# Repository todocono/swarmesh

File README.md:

# Swarm Mesh Research Team

To read the latest research published by the team, access: 
https://github.com/todocono/swarmesh/blob/master/DOC/Paper/SWARM_2019_paper.pdf

To work with the PCB, you will need the latest version of Eagle: https://www.autodesk.com/products/eagle/overview 

To work with the 3D models, you will need Fusion 360 and access the following files:
https://a360.co/2WSIKhr
https://a360.co/2x0crTh

To work with the IDE and latest version, you need:

- Arduino IDE 1.8.9
- CP2102 driver (https://www.silabs.com/products/development-tools/software/usb-to-uart-bridge-vcp-drivers)
- ESP32 Arduino installed 1.0.2 (add https://raw.githubusercontent.com/espressif/arduino-esp32/gh-pages/package_esp32_index.json)
- FastLED library 3.3.2 (from Boards Manager)
- PainlessMesh 1.4.2 (from Boards Manager)
- ArduinoJson 6.12.0 (from Boards Manager)
- TaskScheduler 3.0.2 (from Boards Manager, not really used)
- AsyncTCP (manual install https://github.com/me-no-dev/AsyncTCP)
- AsyncUDP (available in ESP32's arduino library)

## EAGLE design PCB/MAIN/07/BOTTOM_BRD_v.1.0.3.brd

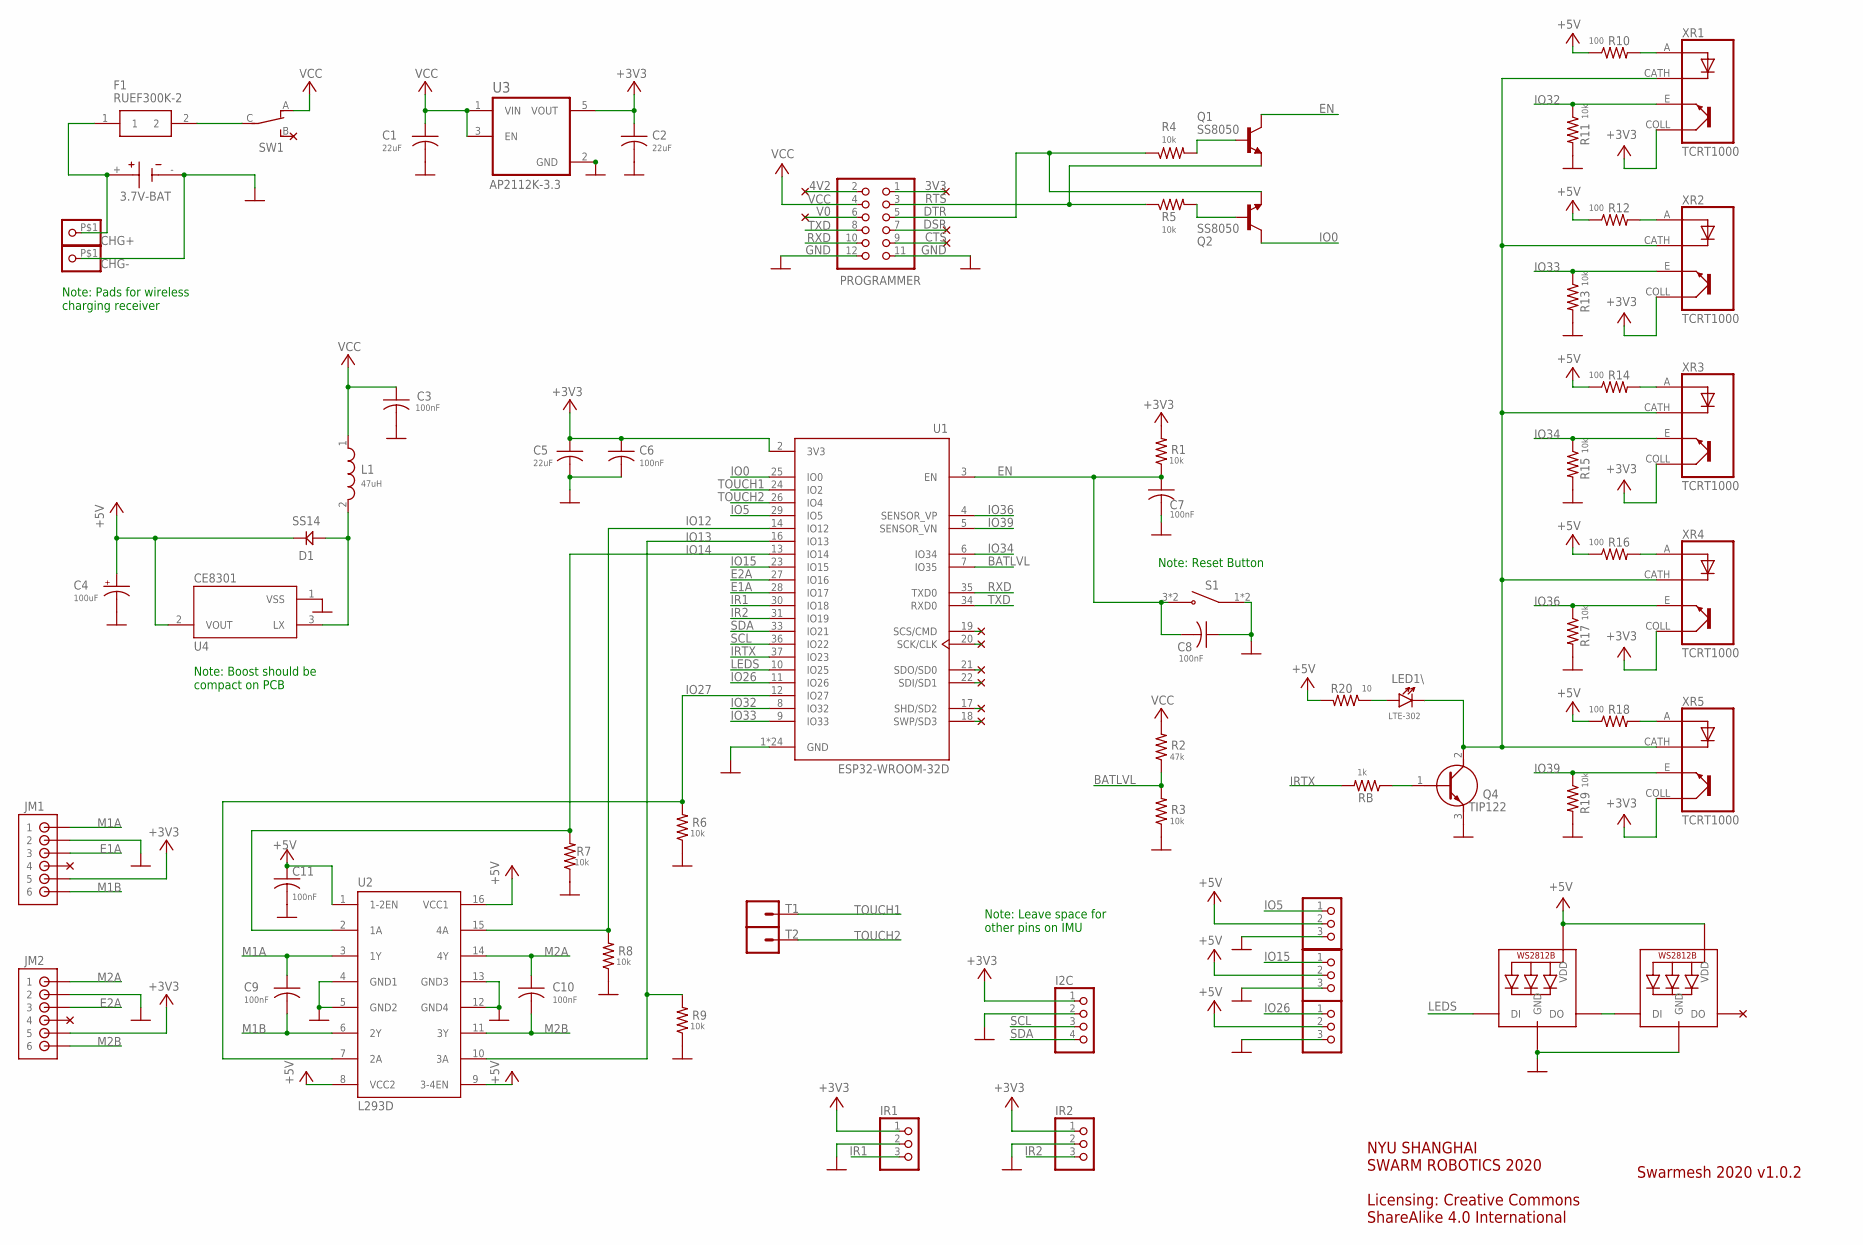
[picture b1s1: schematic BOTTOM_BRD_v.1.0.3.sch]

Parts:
BT: 3.7V-BAT; BAT_6S-AA
C1, C2, C5: 22uF; C0805
C3, C6, C7, C8, C9, C10, C11: 100nF; C0805
C4: 100uF; 153CLV-0605
CHARGING: WS2812B5050; WS2812B
CHG+: PINHD-1X1-BIGPOGO; 1X1-BIGPOGO
CHG-: PINHD-1X1-BIGPOGO; 1X1-BIGPOGO
D1: SS14; DO214
F1: RUEF300K-2; RUEF300K2
GPIO5, GPIO15, GPIO26: PINHD-1X3; 1X03
I2C: PINHD-1X4; 1X04
IR1, IR2: PINHD-1X3; 1X03
JM1, JM2: B6B-ZR
L1: 47uH; INDP5858X480N
LED1\: LTE-302
PROGRAMMER: PINHD-2X6; 2X06
Q1, Q2: SS8050; SOT23
Q4: TIP122; TO270P460X1020X2008-3P
R1, R3, R4, R5, R6, R7, R8, R9, R11, R13, R15, R17, R19: 10k; M0805
R2: 47k; M0805
R10, R12, R14, R16, R18: 100; M0805
R20: 10; M0805
RB: 1k; M0805
S1: 2-1437565-9; SW_2-1437565-9
STATE: WS2812B5050; WS2812B
SW1: CS12ANW03
T1, T2: CONN_01SPRING-CONN; SPRING-CONNECTOR
U1: ESP32-WROOM-32D; MODULE_ESP32-WROOM-32D
U2: L293D; DIL16
U3: AP2112K-3.3; SOT95P285X140-5N
U4: CE8301; REG_MCP1702T-3302E/MB
XR1, XR2, XR3, XR4, XR5: TCRT1000; XDCR_TCRT1000

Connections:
3V3: PROGRAMMER.1
4V2: PROGRAMMER.2
+3V3: C2.1, C5.1, C6.1, I2C.1, IR1.1, IR2.1, JM1.5, JM2.5, R1.2, U1.2 (3V3), U3.5 (VOUT), XR1.COLL (CO), XR2.COLL (CO), XR3.COLL (CO), XR4.COLL (CO), XR5.COLL (CO)
+5V: C4.+, C11.1, CHARGING.1-VDD (VDD), D1.CATHODE (KATHODE), GPIO5.2, GPIO15.2, GPIO26.2, R10.1, R12.1, R14.1, R16.1, R18.1, R20.2, STATE.1-VDD (VDD), U2.1 (1-2EN), U2.8 (VCC2), U2.9 (3-4EN), U2.16 (VCC1), U4.2 (VOUT)
BATLVL: R2.1, R3.2, U1.7 (IO35)
CTS: PROGRAMMER.9
DSR: PROGRAMMER.7
DTR: PROGRAMMER.5, Q2.2 (E), R4.1
E1A: JM1.3, U1.28 (IO17)
E2A: JM2.3, U1.27 (IO16)
EN: C7.1, C8.2, Q1.3 (C), R1.1, S1.3 (NO), S1.4 (NO), U1.3 (EN)
GND: BT.-, C1.2, C2.2, C3.2, C4.-, C5.2, C6.2, C7.2, C8.1, C11.2, CHARGING.3-GND (GND), CHG-.P$1, GPIO5.3, GPIO15.3, GPIO26.3, I2C.2, IR1.2, IR2.2, JM1.2, JM2.2, PROGRAMMER.11, PROGRAMMER.12, Q4.3 (E), R3.1, R6.1, R7.1, R8.1, R9.1, R11.2, R13.2, R15.2, R17.2, R19.2, S1.1 (COM), S1.2 (COM), STATE.3-GND (GND), U1.1 (GND), U1.15 (GND), U1.38 (GND), U1.39_1 (GND), U1.39_2 (GND), U1.39_3 (GND), U1.39_4 (GND), U1.39_5 (GND), U1.39_6 (GND), U1.39_7 (GND), U1.39_8 (GND), U1.39_9 (GND), U1.39_10 (GND), U1.39_11 (GND), U1.39_12 (GND), U1.39_13 (GND), U1.39_14 (GND), U1.39_15 (GND), U1.39_16 (GND), U1.39_17 (GND), U1.39_18 (GND), U1.39_19 (GND), U1.39_20 (GND), U1.39_21 (GND), U2.4 (GND1), U2.5 (GND2), U2.12 (GND4), U2.13 (GND3), U3.2 (GND), U4.1 (VSS)
IO0: Q2.3 (C), U1.25 (IO0)
IO5: GPIO5.1, U1.29 (IO5)
IO12: R8.2, U1.14 (IO12), U2.15 (4A)
IO13: R9.2, U1.16 (IO13), U2.10 (3A)
IO14: R7.2, U1.13 (IO14), U2.2 (1A)
IO15: GPIO15.1, U1.23 (IO15)
IO26: GPIO26.1, U1.11 (IO26)
IO27: R6.2, U1.12 (IO27), U2.7 (2A)
IO32: R11.1, U1.8 (IO32), XR1.E
IO33: R13.1, U1.9 (IO33), XR2.E
IO34: R15.1, U1.6 (IO34), XR3.E
IO36: R17.1, U1.4 (SENSOR_VP), XR4.E
IO39: R19.1, U1.5 (SENSOR_VN), XR5.E
IR1: IR1.3, U1.30 (IO18)
IR2: IR2.3, U1.31 (IO19)
IRTX: RB.2, U1.37 (IO23)
LEDS: CHARGING.4-DIN (DI), U1.10 (IO25)
M1A: C9.1, JM1.1, U2.3 (1Y)
M1B: C9.2, JM1.6, U2.6 (2Y)
M2A: C10.1, JM2.1, U2.14 (4Y)
M2B: C10.2, JM2.6, U2.11 (3Y)
unnamed: BT.+, CHG+.P$1, F1.1
unnamed: Q4.1 (B), RB.1
unnamed: F1.2, SW1.C
unnamed: D1.ANODE, L1.2, U4.3 (LX)
unnamed: R12.2, XR2.A
unnamed: R16.2, XR4.A
unnamed: LED1\.C, Q4.2 (C), XR1.CATH (C), XR2.CATH (C), XR3.CATH (C), XR4.CATH (C), XR5.CATH (C)
unnamed: CHARGING.2-DOUT (DO), STATE.4-DIN (DI)
unnamed: R14.2, XR3.A
unnamed: R18.2, XR5.A
unnamed: Q1.1 (B), R4.2
unnamed: R10.2, XR1.A
unnamed: LED1\.A, R20.1
unnamed: Q2.1 (B), R5.2
RTS: PROGRAMMER.3, Q1.2 (E), R5.1
RXD: PROGRAMMER.10, U1.35 (TXD0)
SCL: I2C.3, U1.36 (IO22)
SDA: I2C.4, U1.33 (IO21)
TOUCH1: T1.P$2, U1.24 (IO2)
TOUCH2: T2.P$2, U1.26 (IO4)
TXD: PROGRAMMER.8, U1.34 (RXD0)
V0: PROGRAMMER.6
VCC: C1.1, C3.1, L1.1, PROGRAMMER.4, R2.2, SW1.A, U3.1 (VIN), U3.3 (EN)

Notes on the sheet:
Note: Pads for wireless charging receiver
Note: Boost should be compact on PCB
Note: Leave space for other pins on IMU
Note: Reset Button
Swarmesh 2020 v1.0.2
NYU SHANGHAI SWARM ROBOTICS 2020 Licensing: Creative Commons ShareAlike 4.0 International

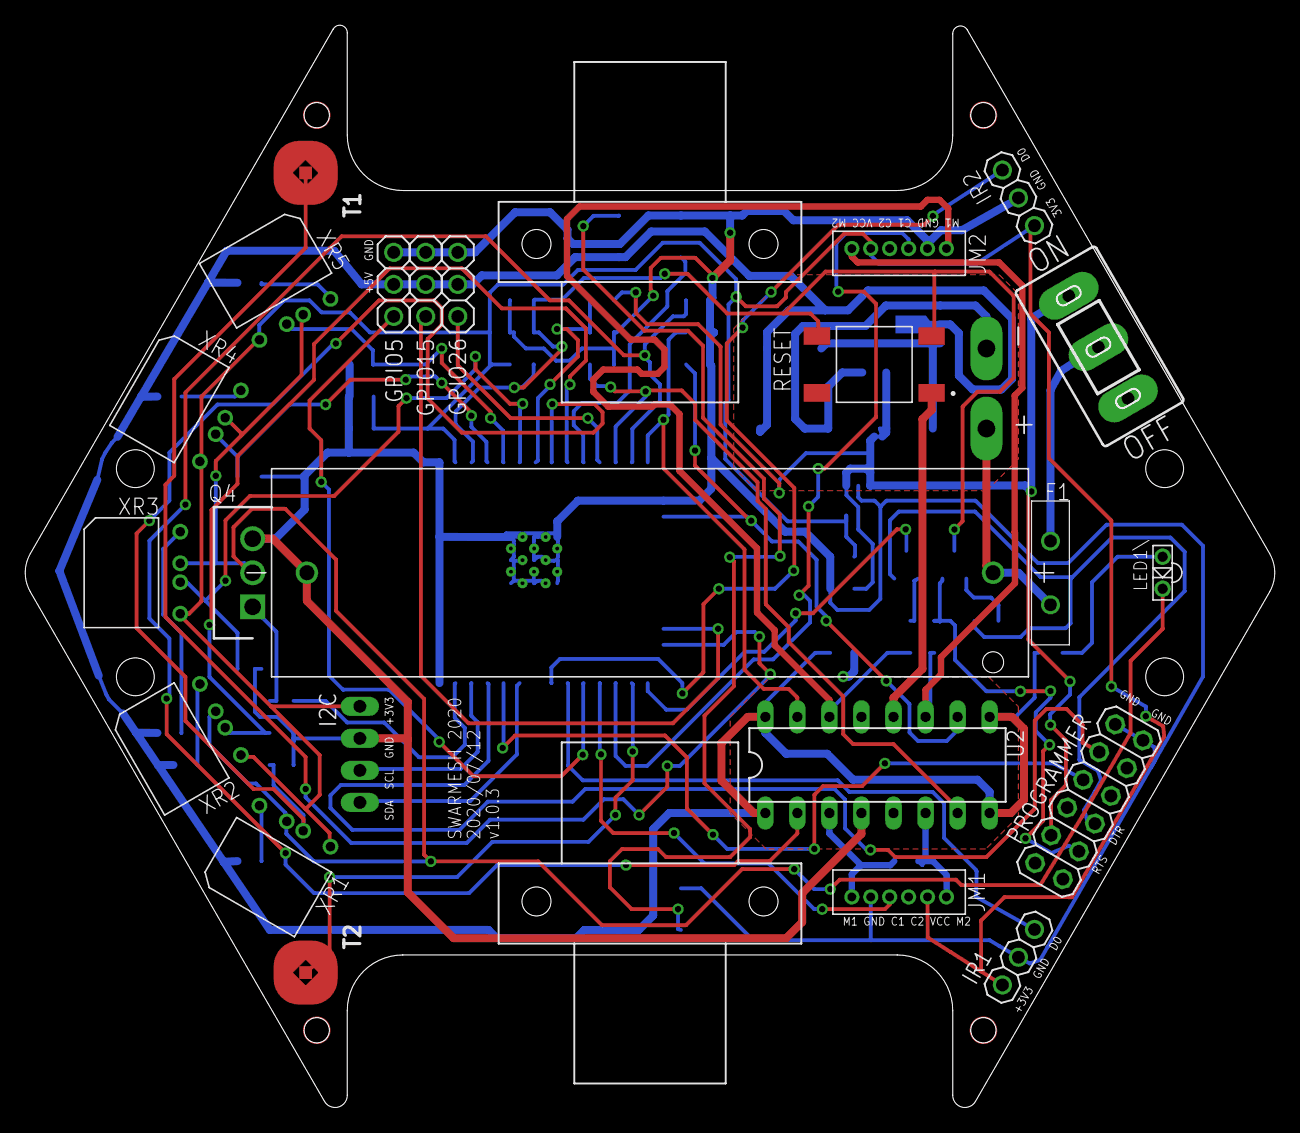
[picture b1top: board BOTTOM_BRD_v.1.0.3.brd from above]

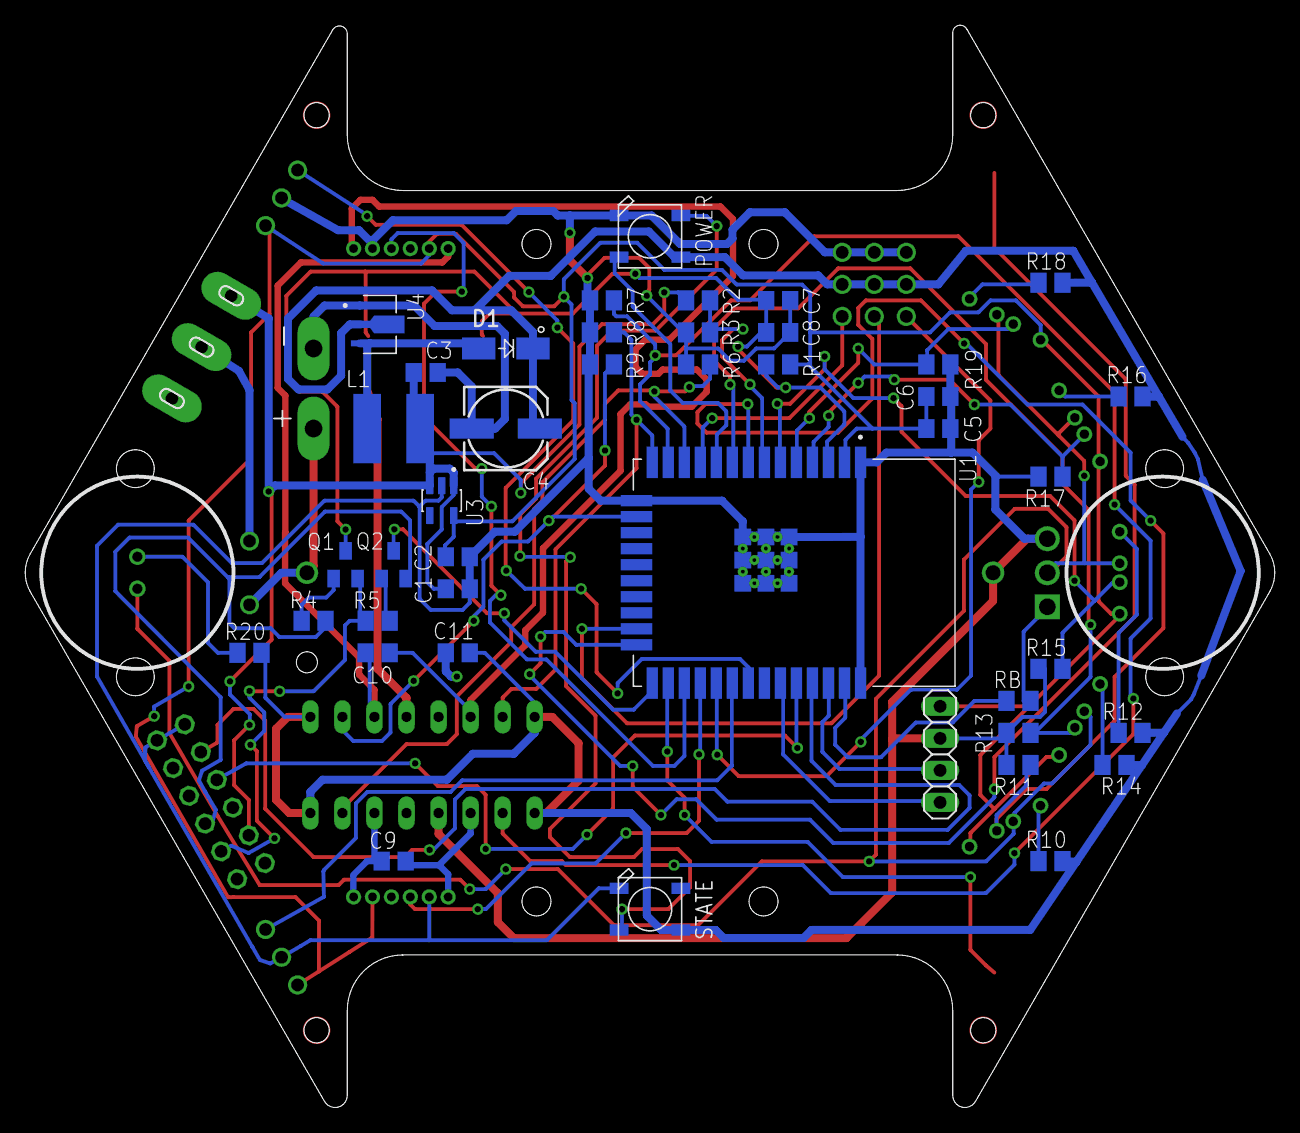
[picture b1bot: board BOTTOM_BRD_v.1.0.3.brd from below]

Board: 2 copper layers, 99.1 x 85.8 mm, 66 parts (43 on the bottom side), 51 nets.

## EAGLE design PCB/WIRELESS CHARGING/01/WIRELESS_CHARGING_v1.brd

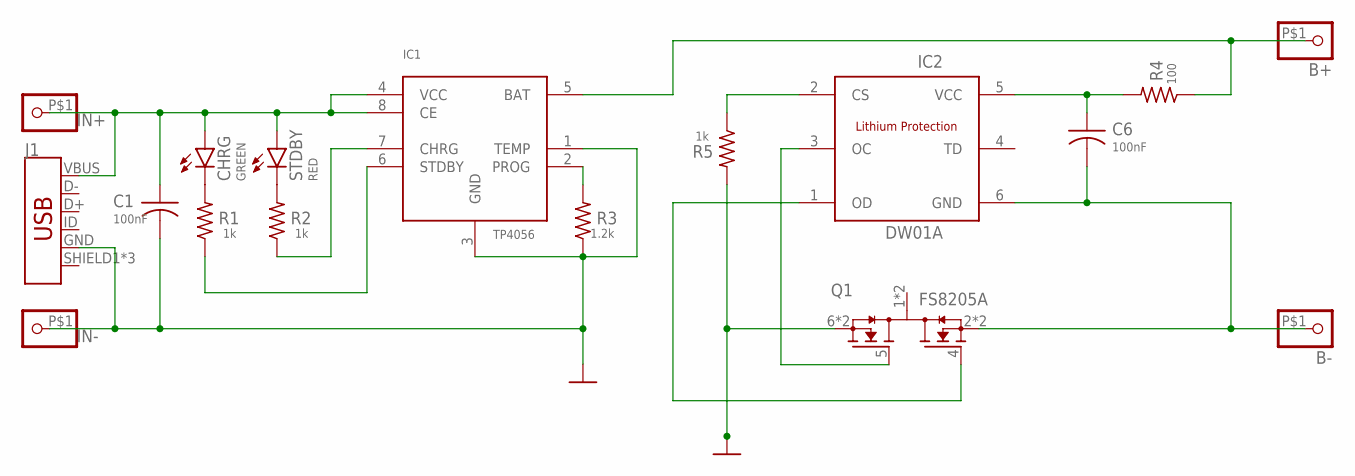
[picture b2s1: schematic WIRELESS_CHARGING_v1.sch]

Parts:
B+: PINHD-1X1-BIGPOGO; 1X1-BIGPOGO
B-: PINHD-1X1-BIGPOGO; 1X1-BIGPOGO
C1, C6: 100nF; C0805
CHRG: GREEN; CHIP-LED0805
IC1: TP4056; SOP-8
IC2: DW01A; SOT23-6
IN+: PINHD-1X1-BIGPOGO; 1X1-BIGPOGO
IN-: PINHD-1X1-BIGPOGO; 1X1-BIGPOGO
J1: USB_MICRO-B_FEMALE-SMT; USB-B-MICRO-SMD
Q1: FS8205A; SOP65P640X120-8N
R1, R2, R5: 1k; M0805
R3: 1.2k; M0805
R4: 100; M0805
STDBY: RED; CHIP-LED0805

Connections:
GND: C1.2, IC1.1 (TEMP), IC1.3 (GND), IN-.P$1, J1.GND, Q1.6 (S2), Q1.7 (S2), R3.1, R5.2
unnamed: C1.1, CHRG.A, IC1.4 (VCC), IC1.8 (CE), IN+.P$1, J1.VBUS, STDBY.A
unnamed: IC1.6 (STDBY), R1.1
unnamed: CHRG.C, R1.2
unnamed: R2.2, STDBY.C
unnamed: IC1.7 (CHRG), R2.1
unnamed: IC1.2 (PROG), R3.2
unnamed: C6.1, IC2.5 (VCC), R4.2
unnamed: B-.P$1, C6.2, IC2.6 (GND), Q1.2 (S1), Q1.3 (S1)
unnamed: B+.P$1, IC1.5 (BAT), R4.1
unnamed: IC2.2 (CS), R5.1
unnamed: IC2.1 (OD), Q1.4 (G1)
unnamed: IC2.3 (OC), Q1.5 (G2)

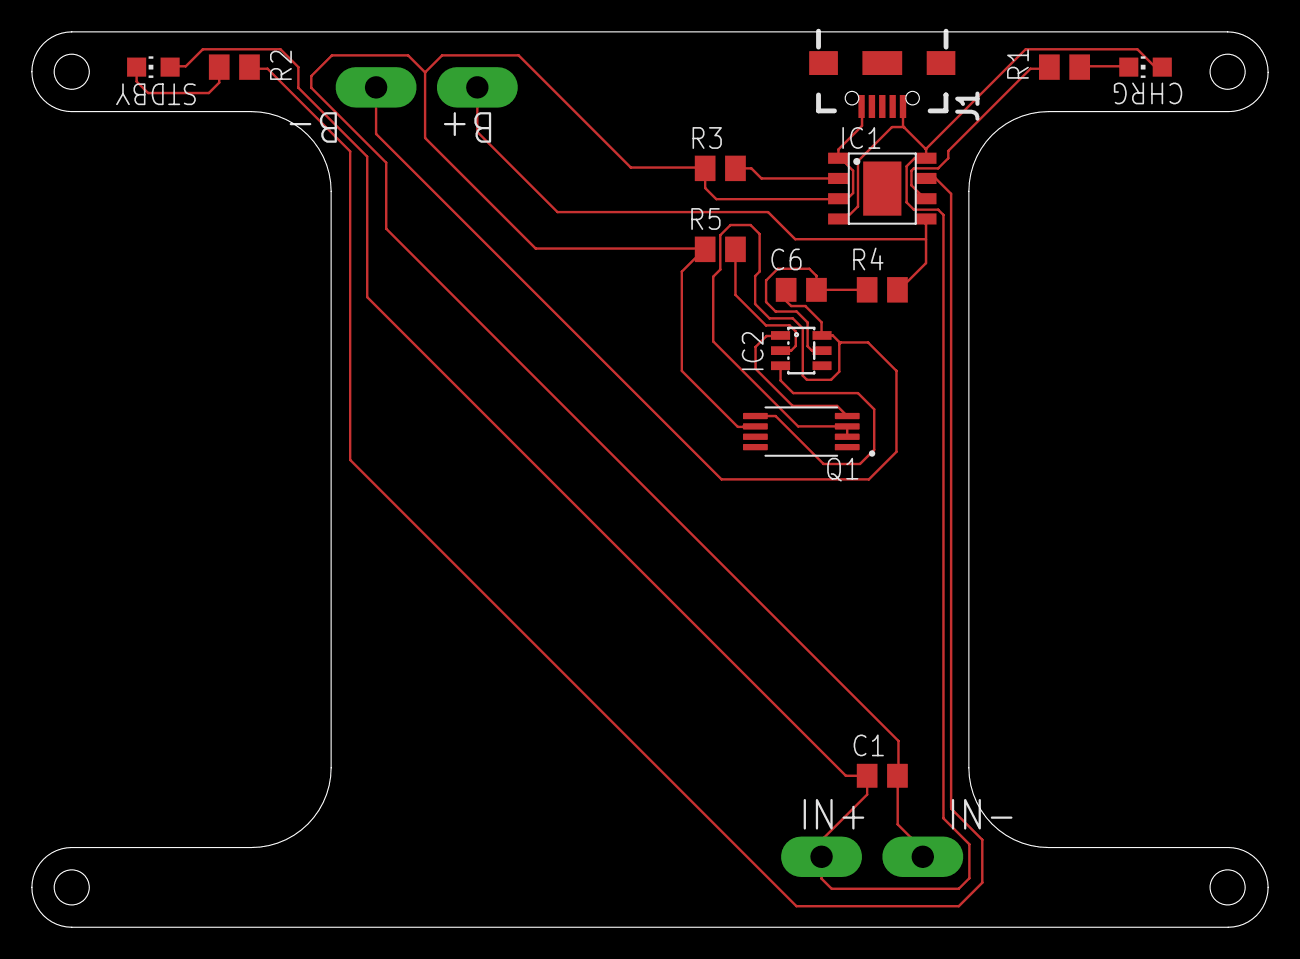
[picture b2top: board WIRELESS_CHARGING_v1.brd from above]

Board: 2 copper layers, 77.5 x 56.2 mm, 17 parts (0 on the bottom side), 13 nets.

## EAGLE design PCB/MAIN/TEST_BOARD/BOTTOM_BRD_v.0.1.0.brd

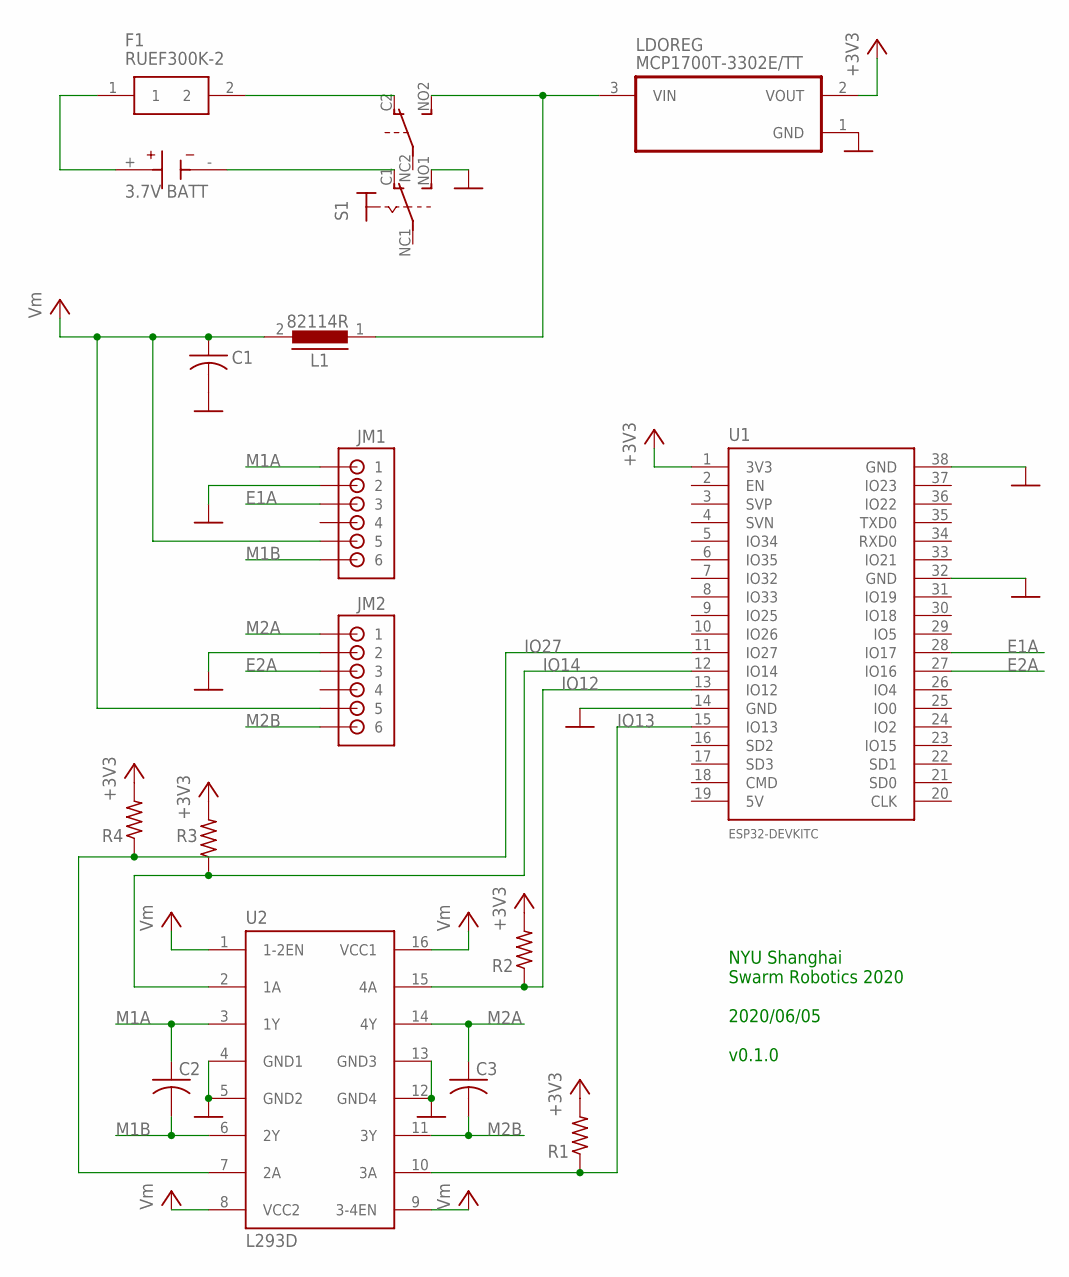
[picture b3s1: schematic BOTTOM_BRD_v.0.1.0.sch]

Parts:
BT1: 3.7V BATT; BAT_6S-AA
C1: C-US025-030X050; C025-030X050
C2, C3: C-US025-025X050; C025-025X050
F1: RUEF300K-2; RUEF300K2
JM1, JM2: B6B-ZR
L1: 82114R
LDOREG: MCP1700T-3302E/TT; SOT95P237X112-3N
R1, R2, R3, R4: R-US_0207/9; 0207/9
S1: SWITCH_320-938; PS22F03
U1: ESP32DEVKITC; ESP32-DEVKITC
U2: L293D; DIL16

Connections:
+3V3: LDOREG.2 (VOUT), R1.2, R2.2, R3.2, R4.2, U1.1 (3V3)
E1A: JM1.3, U1.28 (IO17)
E2A: JM2.3, U1.27 (IO16)
GND: C1.2, JM1.2, JM2.2, LDOREG.1 (GND), S1.NO1 (S), U1.14 (GND), U1.32 (GND), U1.38 (GND), U2.4 (GND1), U2.5 (GND2), U2.12 (GND4), U2.13 (GND3)
IO12: R2.1, U1.13 (IO12), U2.15 (4A)
IO13: R1.1, U1.15 (IO13), U2.10 (3A)
IO14: R3.1, U1.12 (IO14), U2.2 (1A)
IO27: R4.1, U1.11 (IO27), U2.7 (2A)
M1A: C2.1, JM1.1, U2.3 (1Y)
M1B: C2.2, JM1.6, U2.6 (2Y)
M2A: C3.1, JM2.1, U2.14 (4Y)
M2B: C3.2, JM2.6, U2.11 (3Y)
unnamed: BT1.+, F1.1
unnamed: F1.2, S1.C2 (O)
unnamed: BT1.-, S1.C1 (O)
unnamed: L1.1, LDOREG.3 (VIN), S1.NO2 (S)
VCC: C1.1, JM1.5, JM2.5, L1.2, U2.1 (1-2EN), U2.8 (VCC2), U2.9 (3-4EN), U2.16 (VCC1)

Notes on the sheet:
NYU Shanghai Swarm Robotics 2020 2020/06/05 v0.1.0

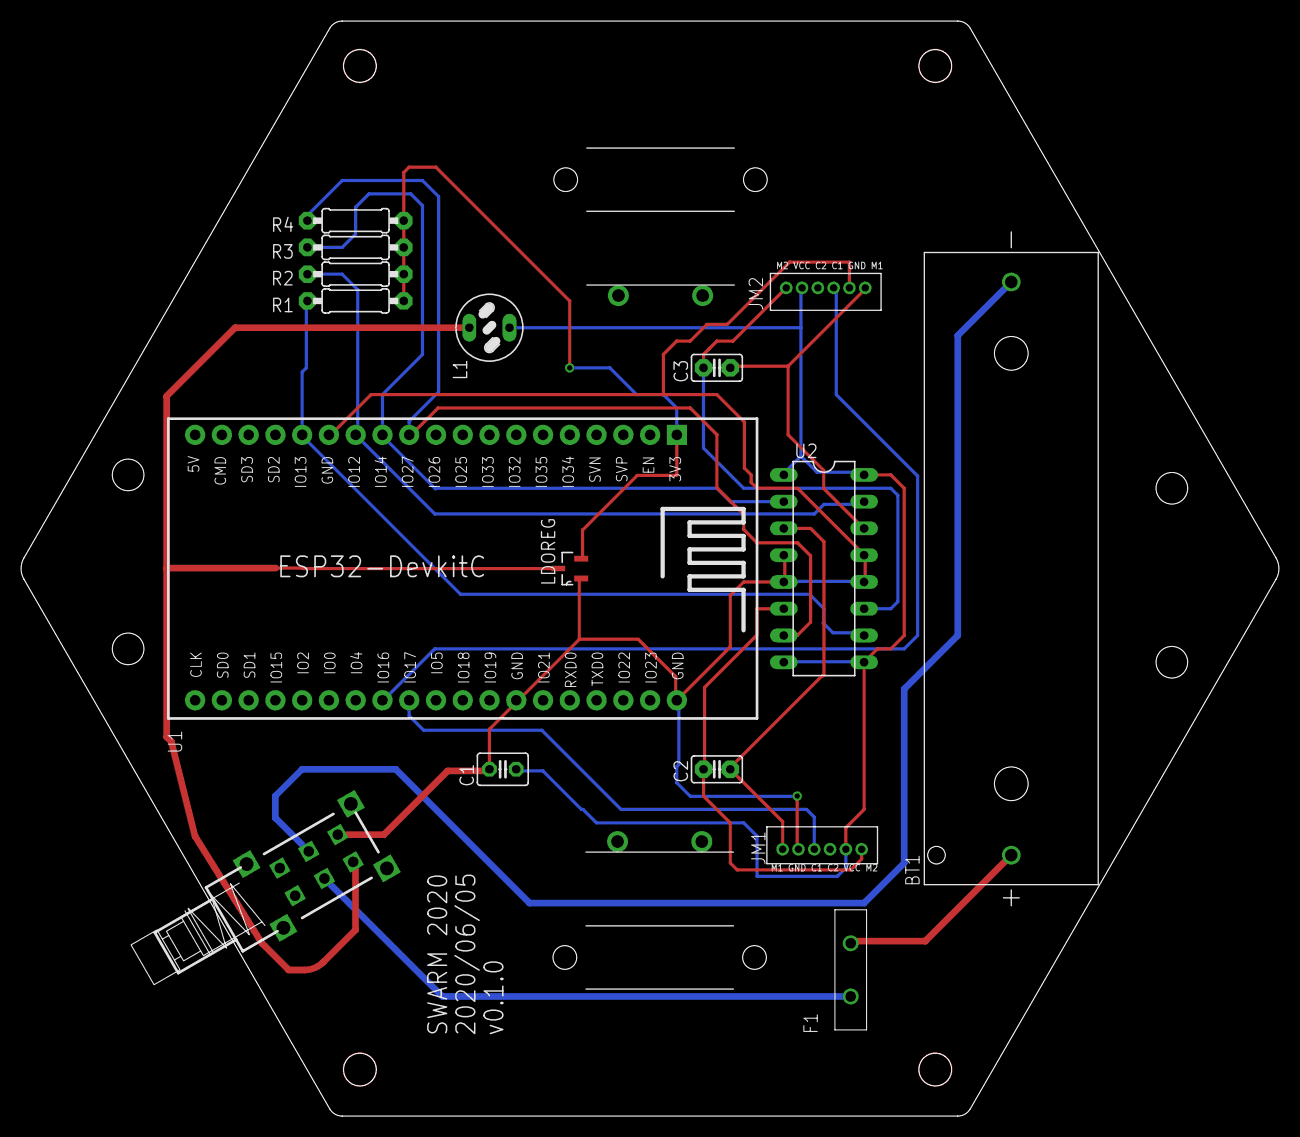
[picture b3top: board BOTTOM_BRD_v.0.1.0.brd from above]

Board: 2 copper layers, 119.4 x 103.9 mm, 18 parts (0 on the bottom side), 17 nets.

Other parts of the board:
U$1, U$7: MOTOR10MM; VIBE-MOTOR-10MM

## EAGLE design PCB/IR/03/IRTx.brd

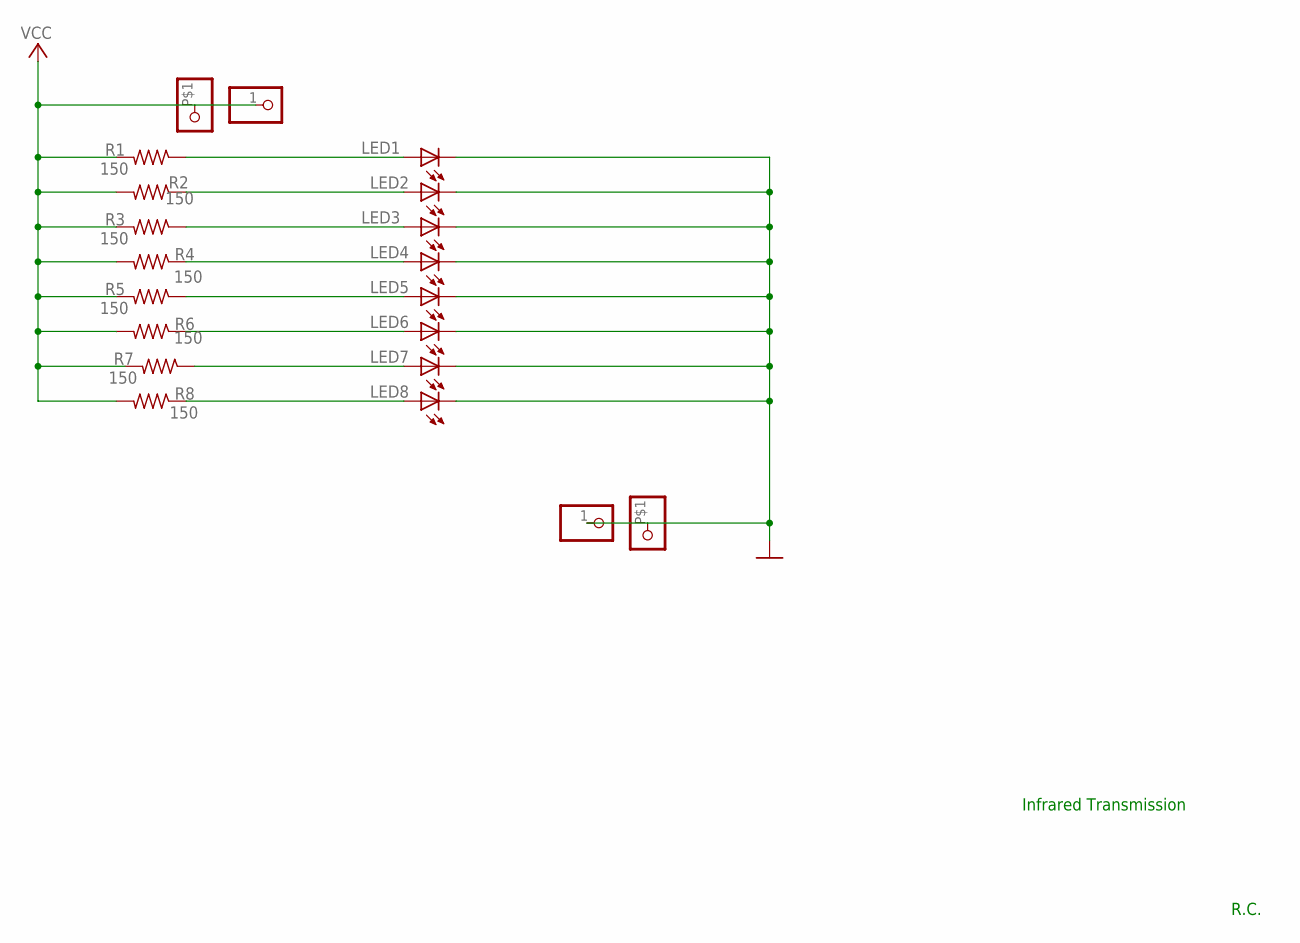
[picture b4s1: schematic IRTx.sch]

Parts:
JP1: 3.3; 1X1-BIGPOGO
JP2: GND; 1X1-BIGPOGO
JP3, JP4: PINHD-1X1; 1X01
LED1, LED2, LED3, LED4, LED5, LED6, LED7, LED8: LED5MM
R1, R2, R3, R4, R5, R6, R7, R8: 150; 0207/10

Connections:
GND: JP2.P$1, JP4.1, LED1.K (C), LED2.K (C), LED3.K (C), LED4.K (C), LED5.K (C), LED6.K (C), LED7.K (C), LED8.K (C)
unnamed: LED2.A, R2.1
unnamed: LED1.A, R1.1
unnamed: LED3.A, R3.1
unnamed: LED4.A, R4.1
unnamed: LED5.A, R5.1
unnamed: LED6.A, R6.1
unnamed: LED7.A, R7.1
unnamed: LED8.A, R8.1
VCC: JP1.P$1, JP3.1, R1.2, R2.2, R3.2, R4.2, R5.2, R6.2, R7.2, R8.2

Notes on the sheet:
Infrared Transmission
R.C.

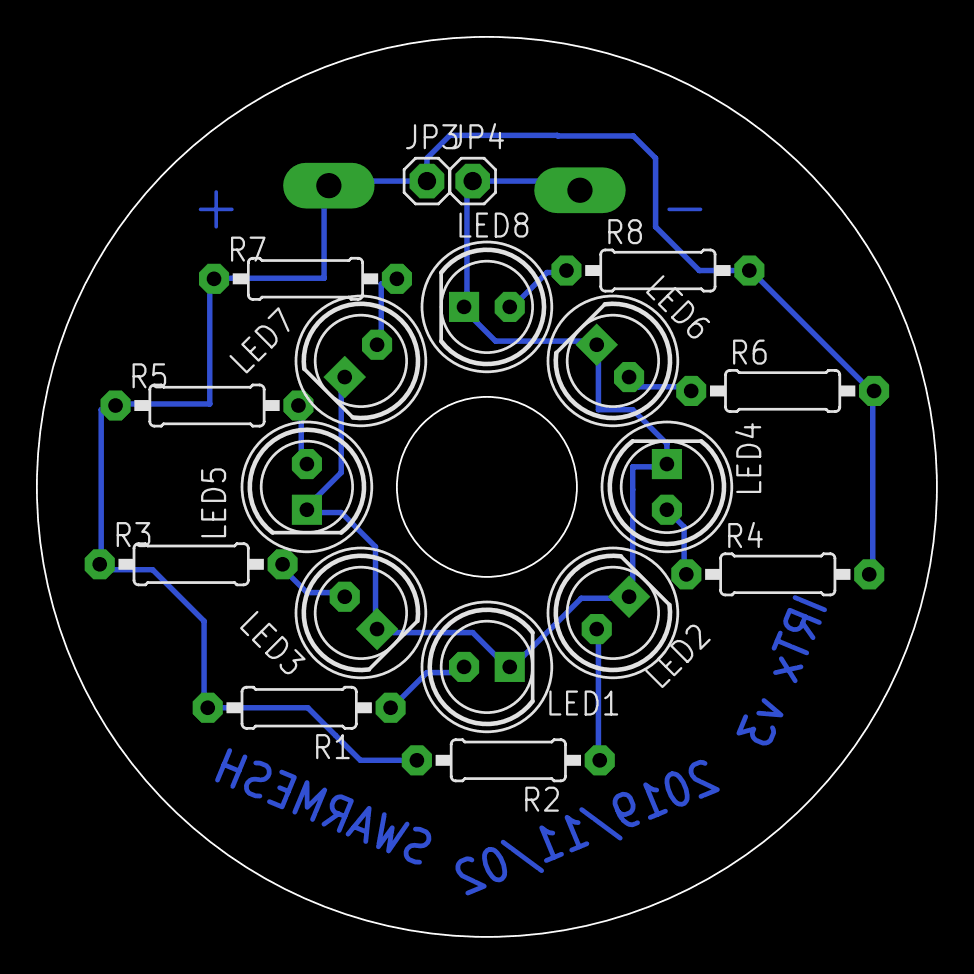
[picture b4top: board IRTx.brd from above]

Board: 2 copper layers, 50.0 x 50.0 mm, 20 parts (0 on the bottom side), 10 nets.

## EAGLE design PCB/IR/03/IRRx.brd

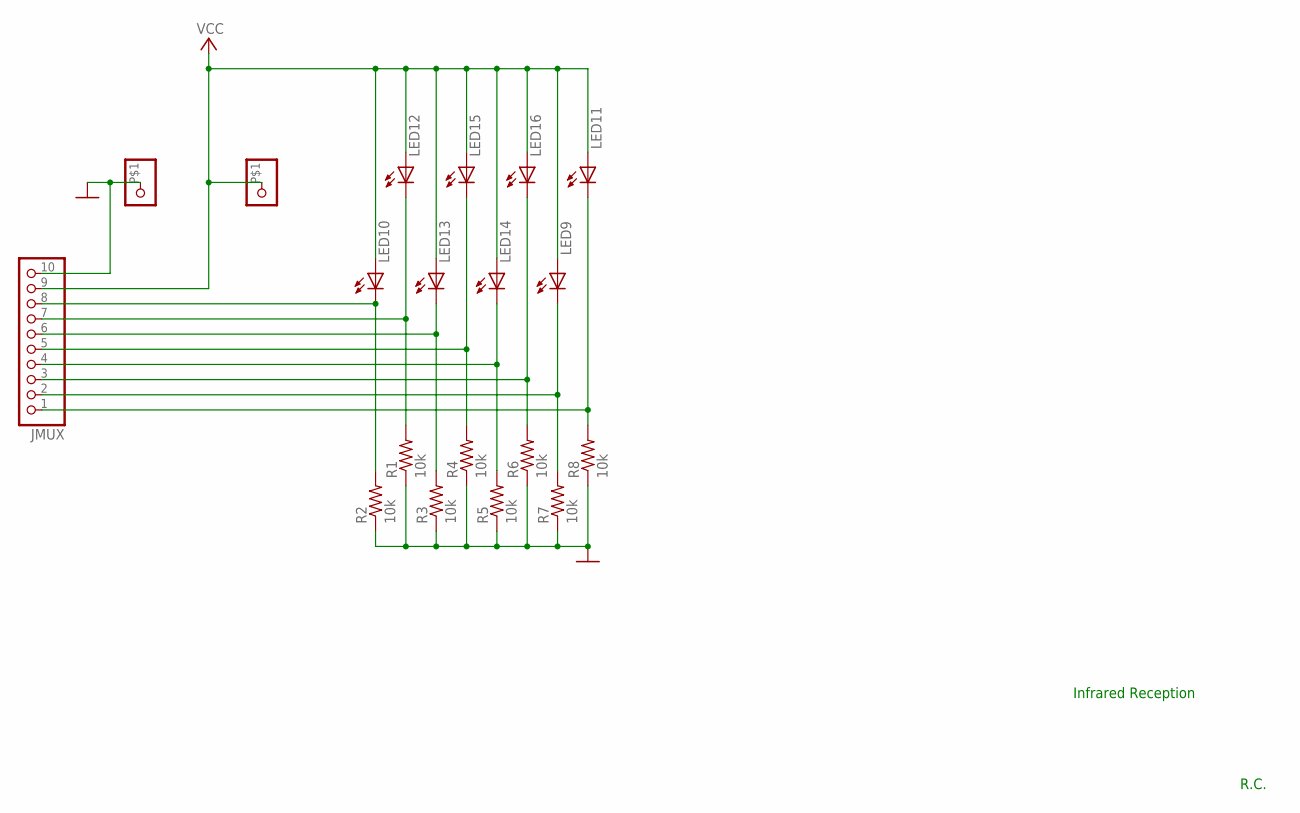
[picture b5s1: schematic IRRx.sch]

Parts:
JMUX: PINHD-1X10; 1X10-BIG
JP1: 3.3; 1X1-BIGPOGO
JP2: GND; 1X1-BIGPOGO
LED9, LED10, LED11, LED12, LED13, LED14, LED15, LED16: LED5MM
R1, R2, R3, R4, R5, R6, R7, R8: 10k; 0207/10

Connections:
GND: JMUX.10, JP2.P$1, R1.1, R2.1, R3.1, R4.1, R5.1, R6.1, R7.1, R8.1
unnamed: JMUX.8, LED10.K (C), R2.2
unnamed: JMUX.7, LED12.K (C), R1.2
unnamed: JMUX.6, LED13.K (C), R3.2
unnamed: JMUX.5, LED15.K (C), R4.2
unnamed: JMUX.4, LED14.K (C), R5.2
unnamed: JMUX.3, LED16.K (C), R6.2
unnamed: JMUX.2, LED9.K (C), R7.2
unnamed: JMUX.1, LED11.K (C), R8.2
VCC: JMUX.9, JP1.P$1, LED9.A, LED10.A, LED11.A, LED12.A, LED13.A, LED14.A, LED15.A, LED16.A

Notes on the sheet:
Infrared Reception
R.C.

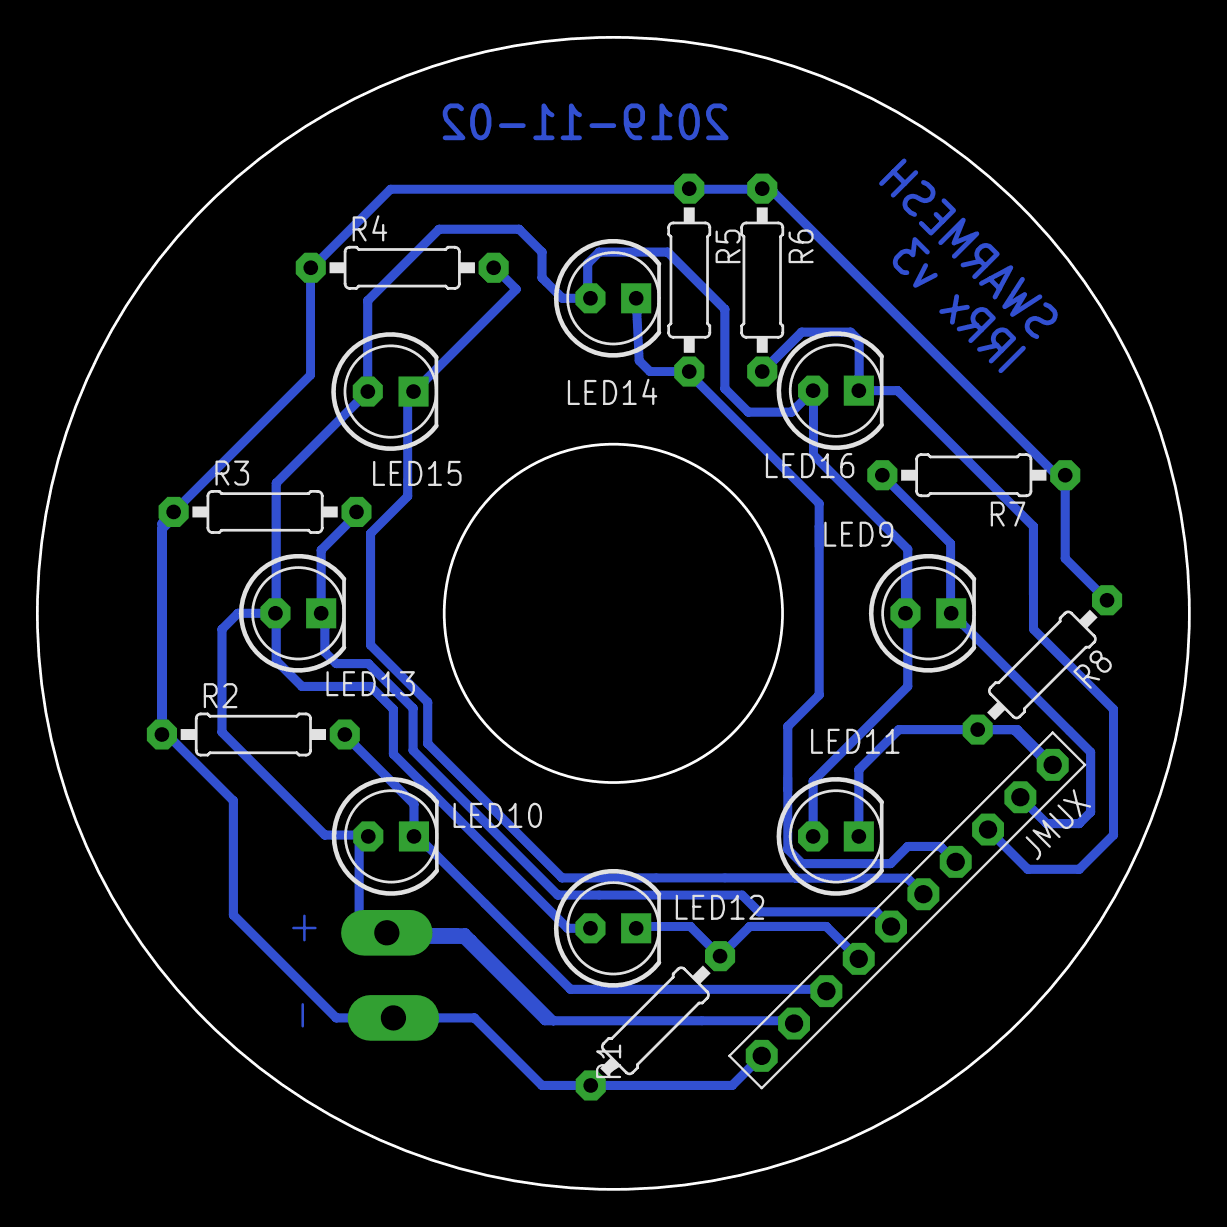
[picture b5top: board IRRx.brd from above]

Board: 2 copper layers, 64.0 x 64.0 mm, 19 parts (0 on the bottom side), 10 nets.
